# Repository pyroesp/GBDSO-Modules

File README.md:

# GBDSO Modules

This repository will include one or more schematics and PCBs based on the [GBDSO repository](https://github.com/pyroesp/GBDSO).  
In here I'll be making modules of the GBDSO schematic so that I can test them individually.  

A motherboard PCB will also be made so that all modules can be attached to each other and tested as a whole.  

Not sure yet how I'm going to set this up, but I'd like to keep everything related to the modules and motherboard in this repository.

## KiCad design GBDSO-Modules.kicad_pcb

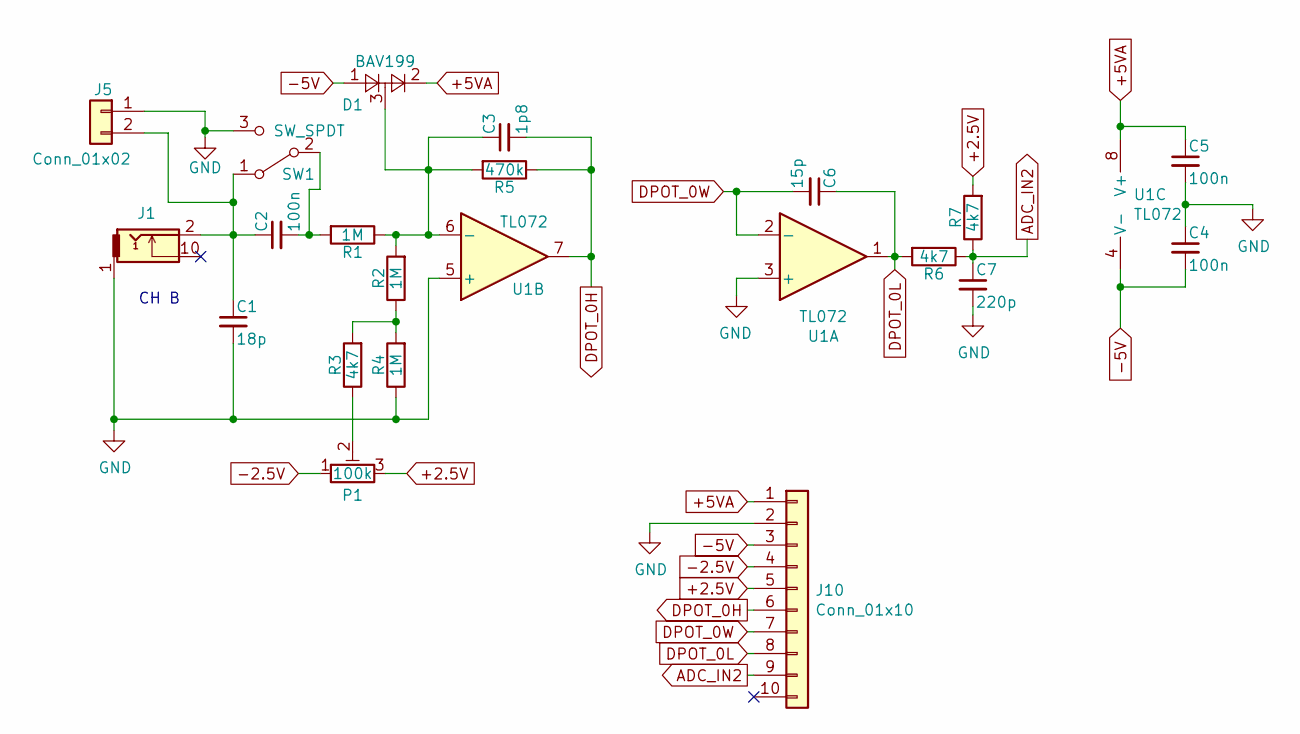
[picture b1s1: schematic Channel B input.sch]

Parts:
C1: 18p; C_0805_2012Metric
C2, C4, C5: 100n; C_0805_2012Metric
C3: 1p8; C_0805_2012Metric
C6: 15p; C_0805_2012Metric
C7: 220p; C_0805_2012Metric
D1: BAV199; SOT-23_Handsoldering
J1: MJ-3523-SMT-TR
J5: Conn_01x02; PinHeader_1x02_P2.54mm_Horizontal
J10: Conn_01x10; DIP-10_W10.16mm
P1: 100k; Potentiometer_Vishay_TS53YJ_Vertical
R1, R2, R4: 1M; R_0805_2012Metric
R3, R6, R7: 4k7; R_0805_2012Metric
R5: 470k; R_0805_2012Metric
SW1: SW_SPDT; SW_SPDT_CK-JS102011SAQN
U1: TL072; SOIC-8_3.9x4.9mm_P1.27mm

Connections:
+2.5V: J10.5, P1.3, R7.2; also elsewhere on the board
+5VA: C5.1, D1.2, J10.1, U1.8 (V+); also elsewhere on the board
-2.5V: J10.4, P1.1; also elsewhere on the board
-5V: C4.2, D1.1, J10.3, U1.4 (V-); also elsewhere on the board
ADC_IN2: C7.1, J10.9, R6.1, R7.1; also elsewhere on the board
DPOT_0H: C3.2, J10.6, R5.1, U1.7; also elsewhere on the board
DPOT_0L: C6.1, J10.8, R6.2, U1.1; also elsewhere on the board
DPOT_0W: C6.2, J10.7, U1.2 (-); also elsewhere on the board
GND: C1.2, C4.1, C5.2, C7.2, J1.1, J5.1, J10.2, R4.1, SW1.3 (C), U1.3 (+), U1.5 (+); also elsewhere on the board
unnamed: C1.1, C2.1, J1.2, J5.2, SW1.1 (A)
unnamed: C2.2, R1.2, SW1.2 (B)
unnamed: C3.1, D1.3, R1.1, R2.2, R5.2, U1.6 (-)
unnamed: P1.2, R3.1
unnamed: R2.1, R3.2, R4.2

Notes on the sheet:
CH B

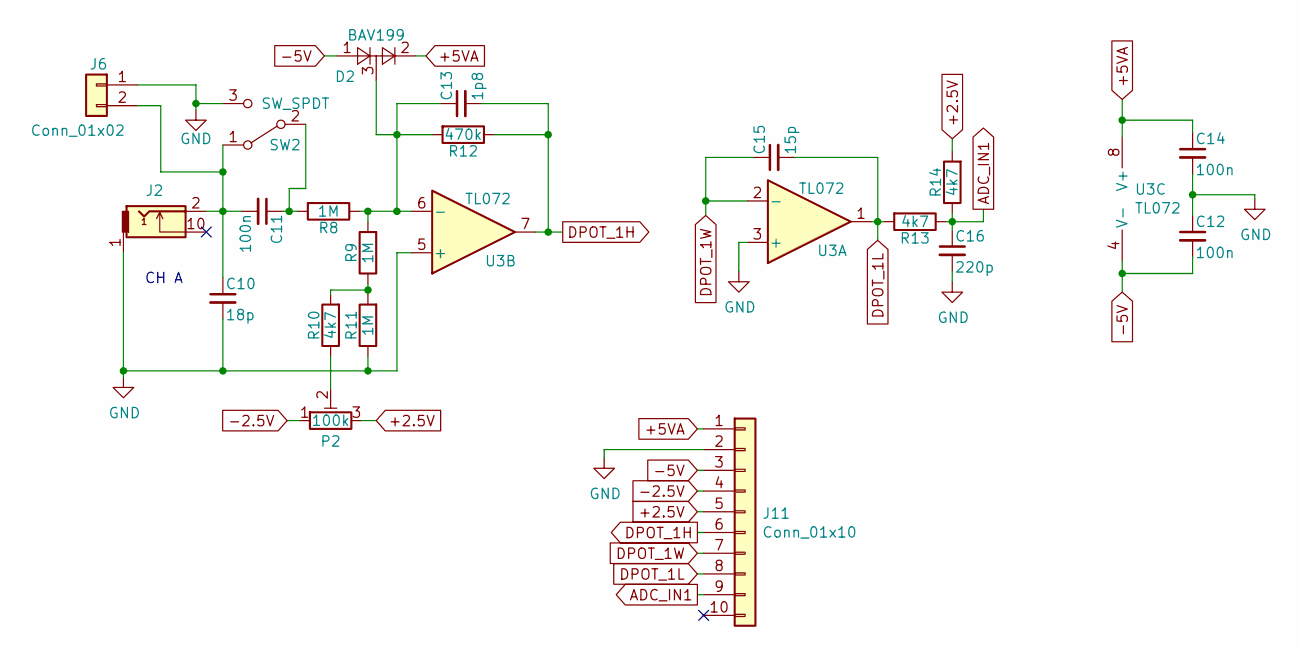
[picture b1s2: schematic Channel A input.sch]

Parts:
C10: 18p; C_0805_2012Metric
C11, C12, C14: 100n; C_0805_2012Metric
C13: 1p8; C_0805_2012Metric
C15: 15p; C_0805_2012Metric
C16: 220p; C_0805_2012Metric
D2: BAV199; SOT-23_Handsoldering
J2: MJ-3523-SMT-TR
J6: Conn_01x02; PinHeader_1x02_P2.54mm_Horizontal
J11: Conn_01x10; DIP-10_W10.16mm
P2: 100k; Potentiometer_Vishay_TS53YJ_Vertical
R8, R9, R11: 1M; R_0805_2012Metric
R10, R13, R14: 4k7; R_0805_2012Metric
R12: 470k; R_0805_2012Metric
SW2: SW_SPDT; SW_SPDT_CK-JS102011SAQN
U3: TL072; SOIC-8_3.9x4.9mm_P1.27mm

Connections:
+2.5V: J11.5, P2.3, R14.2; also elsewhere on the board
+5VA: C14.1, D2.2, J11.1, U3.8 (V+); also elsewhere on the board
-2.5V: J11.4, P2.1; also elsewhere on the board
-5V: C12.2, D2.1, J11.3, U3.4 (V-); also elsewhere on the board
ADC_IN1: C16.1, J11.9, R13.1, R14.1; also elsewhere on the board
DPOT_1H: C13.2, J11.6, R12.1, U3.7; also elsewhere on the board
DPOT_1L: C15.2, J11.8, R13.2, U3.1; also elsewhere on the board
DPOT_1W: C15.1, J11.7, U3.2 (-); also elsewhere on the board
GND: C10.2, C12.1, C14.2, C16.2, J2.1, J6.1, J11.2, R11.1, SW2.3 (C), U3.3 (+), U3.5 (+); also elsewhere on the board
unnamed: C10.1, C11.2, J2.2, J6.2, SW2.1 (A)
unnamed: C11.1, R8.2, SW2.2 (B)
unnamed: C13.1, D2.3, R8.1, R9.2, R12.2, U3.6 (-)
unnamed: P2.2, R10.1
unnamed: R9.1, R10.2, R11.2

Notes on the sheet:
CH A

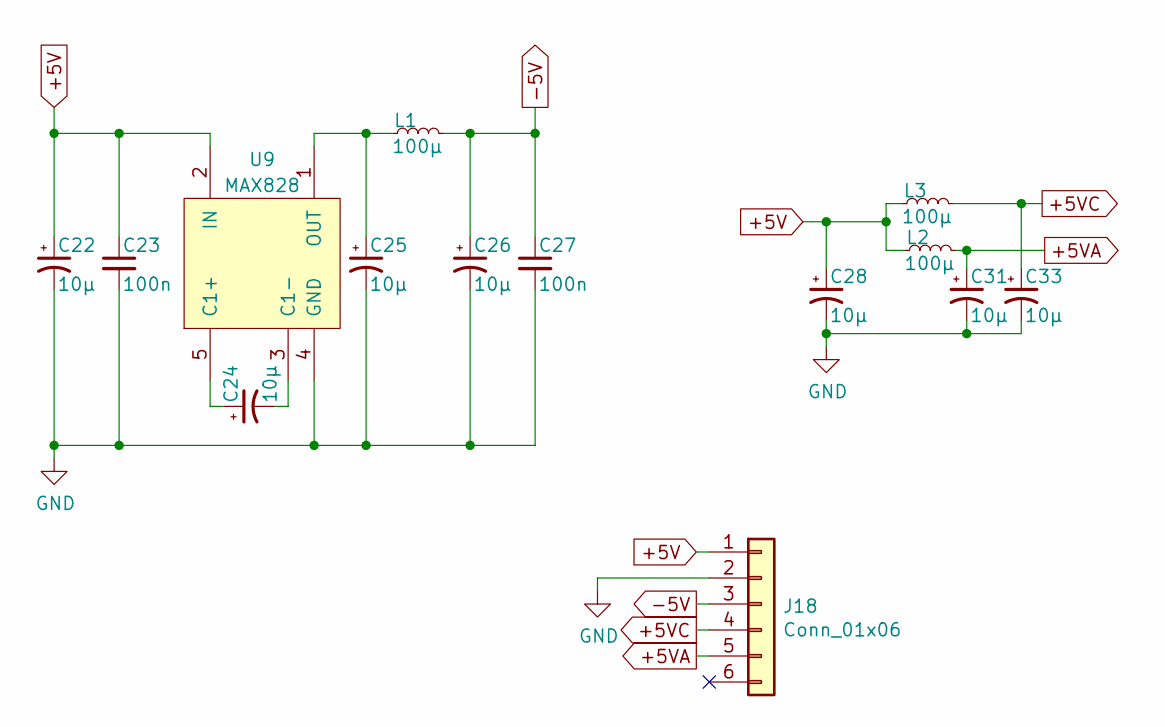
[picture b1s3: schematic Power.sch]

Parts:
C22, C24, C25, C26, C28, C31, C33: 10µ; C_1206_3216Metric
C23, C27: 100n; C_0805_2012Metric
J18: Conn_01x06; DIP-6_W7.62mm
L1, L2, L3: 100µ; L_0805_2012Metric_Pad1.15x1.40mm_HandSolder
U9: MAX828; SOT-23-5_HandSoldering

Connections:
+5V: C22.1, C23.1, C28.1, J18.1, L2.1, L3.1, U9.2 (IN); also elsewhere on the board
+5VA: C31.1, J18.5, L2.2; also elsewhere on the board
+5VC: C33.1, J18.4, L3.2; also elsewhere on the board
-5V: C26.1, C27.1, J18.3, L1.2; also elsewhere on the board
GND: C22.2, C23.2, C25.2, C26.2, C27.2, C28.2, C31.2, C33.2, J18.2, U9.4 (GND); also elsewhere on the board
unnamed: C24.1, U9.5 (C1+)
unnamed: C24.2, U9.3 (C1-)
unnamed: C25.1, L1.1, U9.1 (OUT)

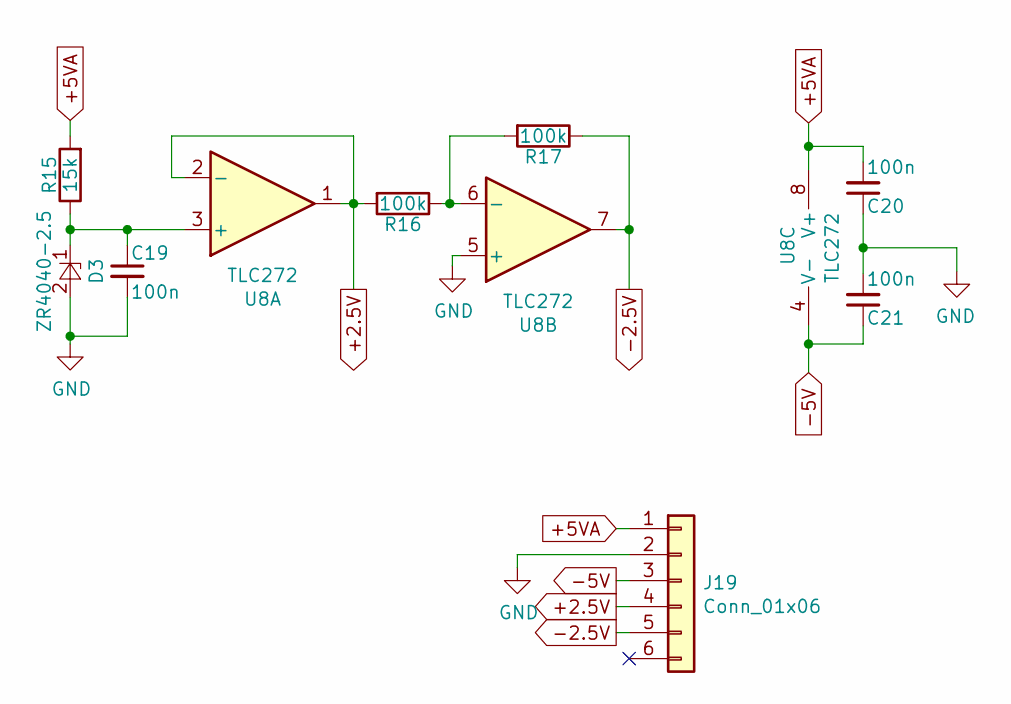
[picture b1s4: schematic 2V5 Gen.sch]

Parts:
C19, C20, C21: 100n; C_0805_2012Metric
D3: ZR4040-2.5; SOT-23_Handsoldering
J19: Conn_01x06; DIP-6_W10.16mm
R15: 15k; R_0805_2012Metric
R16, R17: 100k; R_0805_2012Metric
U8: TLC272; SOIC-8_3.9x4.9mm_P1.27mm

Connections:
+2.5V: J19.4, R16.2, U8.1, U8.2 (-); also elsewhere on the board
+5VA: C20.2, J19.1, R15.2, U8.8 (V+); also elsewhere on the board
-2.5V: J19.5, R17.1, U8.7; also elsewhere on the board
-5V: C21.1, J19.3, U8.4 (V-); also elsewhere on the board
GND: C19.2, C20.1, C21.2, D3.2, J19.2, U8.5 (+); also elsewhere on the board
unnamed: C19.1, D3.1, R15.1, U8.3 (+)
unnamed: R16.1, R17.2, U8.6 (-)

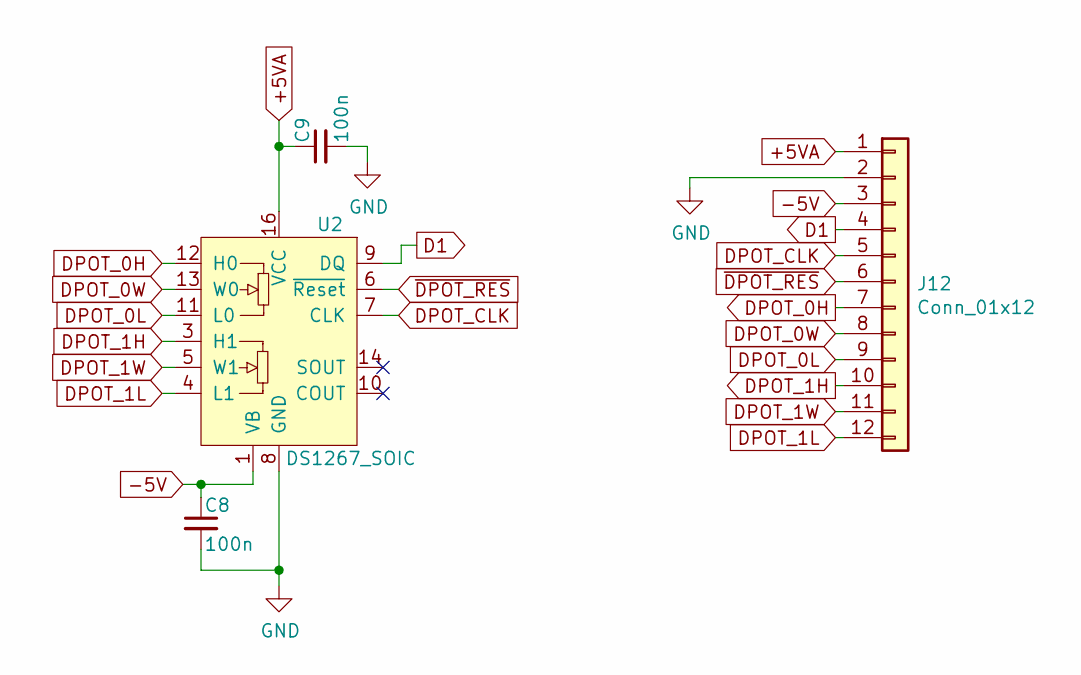
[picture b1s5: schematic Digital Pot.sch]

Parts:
C8, C9: 100n; C_0805_2012Metric
J12: Conn_01x12; PinHeader_1x12_P2.54mm_Vertical
U2: DS1267_SOIC; SOIC-16W_7.5x10.3mm_P1.27mm

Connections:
+5VA: C9.1, J12.1, U2.16 (VCC); also elsewhere on the board
-5V: C8.1, J12.3, U2.1 (VB); also elsewhere on the board
D1: J12.4, U2.9 (DQ); also elsewhere on the board
DPOT_0H: J12.7, U2.12 (H0); also elsewhere on the board
DPOT_0L: J12.9, U2.11 (L0); also elsewhere on the board
DPOT_0W: J12.8, U2.13 (W0); also elsewhere on the board
DPOT_1H: J12.10, U2.3 (H1); also elsewhere on the board
DPOT_1L: J12.12, U2.4 (L1); also elsewhere on the board
DPOT_1W: J12.11, U2.5 (W1); also elsewhere on the board
DPOT_CLK: J12.5, U2.7 (CLK); also elsewhere on the board
GND: C8.2, C9.2, J12.2, U2.8 (GND); also elsewhere on the board
~DPOT_RES: J12.6, U2.6 (~Reset); also elsewhere on the board

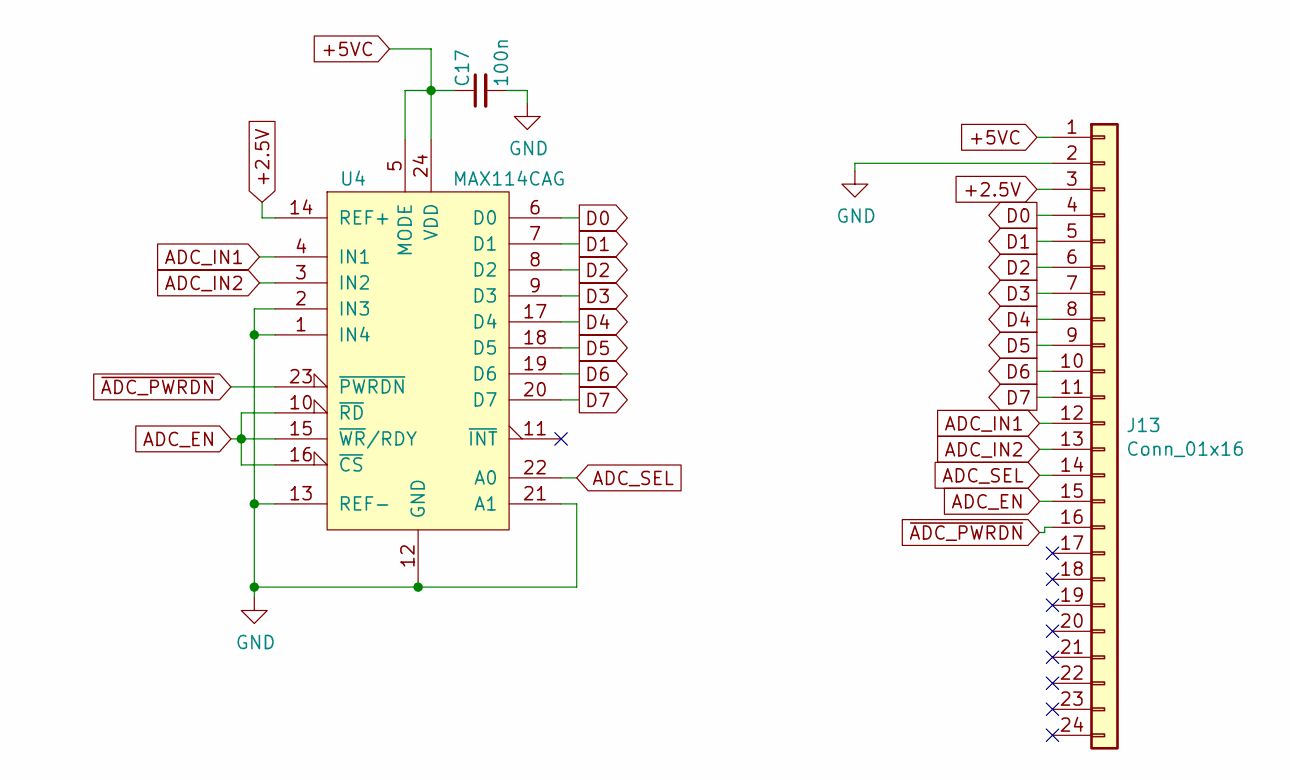
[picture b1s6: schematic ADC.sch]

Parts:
C17: 100n; C_0805_2012Metric
J13: Conn_01x16; DIP-24_W15.24mm
U4: MAX114CAG; SSOP-24_5.3x8.2mm_P0.65mm

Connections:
+2.5V: J13.3, U4.14 (REF+); also elsewhere on the board
+5VC: C17.1, J13.1, U4.5 (MODE), U4.24 (VDD); also elsewhere on the board
ADC_EN: J13.15, U4.10 (~RD), U4.15 (~WR~/RDY), U4.16 (~CS); also elsewhere on the board
ADC_IN1: J13.12, U4.4 (IN1); also elsewhere on the board
ADC_IN2: J13.13, U4.3 (IN2); also elsewhere on the board
ADC_SEL: J13.14, U4.22 (A0); also elsewhere on the board
D0: J13.4, U4.6 (D0); also elsewhere on the board
D1: J13.5, U4.7 (D1); also elsewhere on the board
D2: J13.6, U4.8 (D2); also elsewhere on the board
D3: J13.7, U4.9 (D3); also elsewhere on the board
D4: J13.8, U4.17 (D4); also elsewhere on the board
D5: J13.9, U4.18 (D5); also elsewhere on the board
D6: J13.10, U4.19 (D6); also elsewhere on the board
D7: J13.11, U4.20 (D7); also elsewhere on the board
GND: C17.2, J13.2, U4.1 (IN4), U4.2 (IN3), U4.12 (GND), U4.13 (REF-), U4.21 (A1); also elsewhere on the board
~ADC_PWRDN: J13.16, U4.23 (~PWRDN); also elsewhere on the board

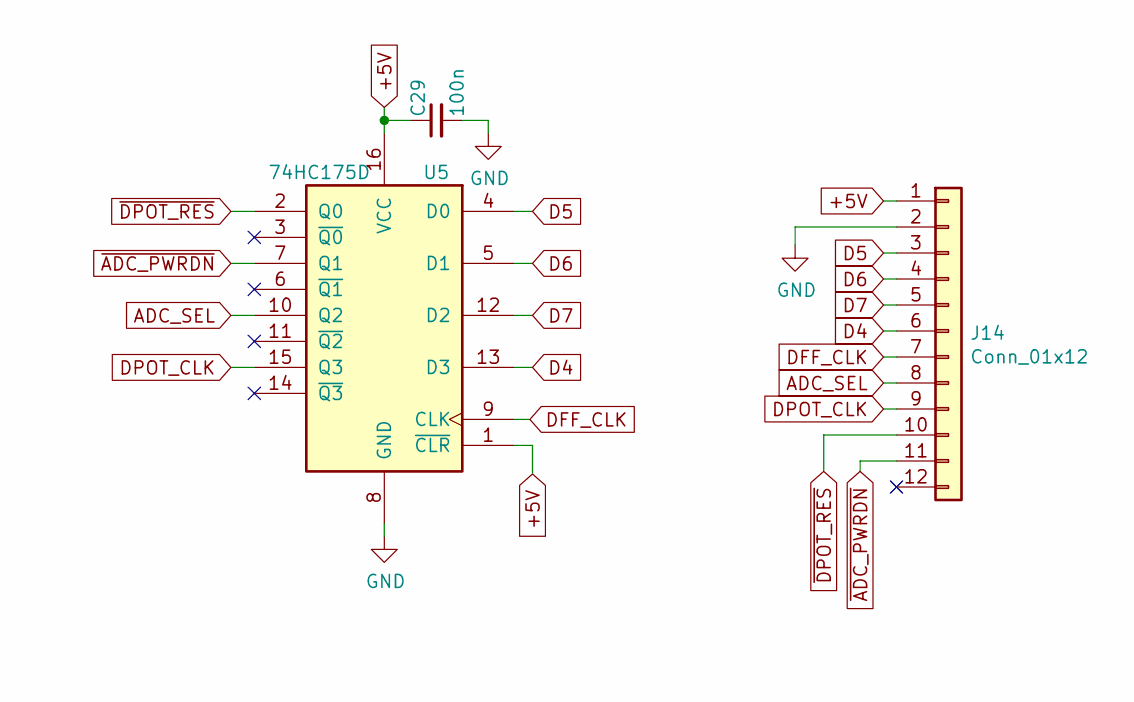
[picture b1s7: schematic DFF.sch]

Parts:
C29: 100n; C_0805_2012Metric
J14: Conn_01x12; DIP-12_W10.16mm_LongPads
U5: 74HC175D; SOIC-16_3.9x9.9mm_P1.27mm

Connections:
+5V: C29.1, J14.1, U5.1 (~CLR), U5.16 (VCC); also elsewhere on the board
ADC_SEL: J14.8, U5.10 (Q2); also elsewhere on the board
D4: J14.6, U5.13 (D3); also elsewhere on the board
D5: J14.3, U5.4 (D0); also elsewhere on the board
D6: J14.4, U5.5 (D1); also elsewhere on the board
D7: J14.5, U5.12 (D2); also elsewhere on the board
DFF_CLK: J14.7, U5.9 (CLK); also elsewhere on the board
DPOT_CLK: J14.9, U5.15 (Q3); also elsewhere on the board
GND: C29.2, J14.2, U5.8 (GND); also elsewhere on the board
~ADC_PWRDN: J14.11, U5.7 (Q1); also elsewhere on the board
~DPOT_RES: J14.10, U5.2 (Q0); also elsewhere on the board

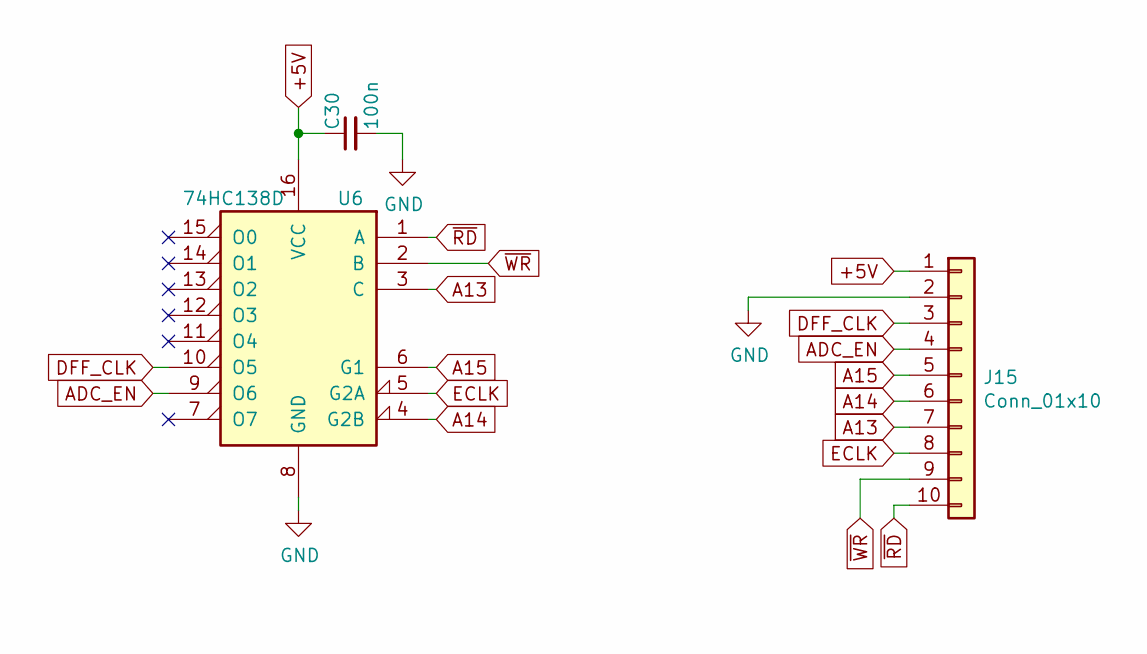
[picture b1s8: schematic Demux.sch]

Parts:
C30: 100n; C_0805_2012Metric
J15: Conn_01x10; DIP-10_W10.16mm
U6: 74HC138D; SOIC-16_3.9x9.9mm_P1.27mm

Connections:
+5V: C30.1, J15.1, U6.16 (VCC); also elsewhere on the board
A13: J15.7, U6.3 (C); also elsewhere on the board
A14: J15.6, U6.4 (G2B); also elsewhere on the board
A15: J15.5, U6.6 (G1); also elsewhere on the board
ADC_EN: J15.4, U6.9 (O6); also elsewhere on the board
DFF_CLK: J15.3, U6.10 (O5); also elsewhere on the board
ECLK: J15.8, U6.5 (G2A); also elsewhere on the board
GND: C30.2, J15.2, U6.8 (GND); also elsewhere on the board
~RD: J15.10, U6.1 (A); also elsewhere on the board
~WR: J15.9, U6.2 (B); also elsewhere on the board

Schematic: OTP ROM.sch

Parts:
C18: 100n; C_0805_2012Metric
J16: Conn_01x28; DIP-28_W7.62mm
JP1: SolderJumper_3_Open; SolderJumper-3_P1.3mm_Open_RoundedPad1.0x1.5mm_NumberLabels
U7: AT27C256R; PLCC-32_HandSolder

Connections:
+5V: C18.1, J16.1, JP1.3 (B), U7.32 (VCC); also elsewhere on the board
A0: J16.5, U7.11 (A0); also elsewhere on the board
A1: J16.6, U7.10 (A1); also elsewhere on the board
A2: J16.7, U7.9 (A2); also elsewhere on the board
A3: J16.8, U7.8 (A3); also elsewhere on the board
A4: J16.9, U7.7 (A4); also elsewhere on the board
A5: J16.10, U7.6 (A5); also elsewhere on the board
A6: J16.11, U7.5 (A6); also elsewhere on the board
A7: J16.12, U7.4 (A7); also elsewhere on the board
A8: J16.13, U7.29 (A8); also elsewhere on the board
A9: J16.14, U7.28 (A9); also elsewhere on the board
A10: J16.15, U7.24 (A10); also elsewhere on the board
A11: J16.16, U7.27 (A11); also elsewhere on the board
A12: J16.17, U7.3 (A12); also elsewhere on the board
A13: J16.18, U7.30 (A13); also elsewhere on the board
A14: J16.19, U7.31 (A14); also elsewhere on the board
A15: J16.20, U7.23 (~CE); also elsewhere on the board
D0: J16.21, U7.13 (D0); also elsewhere on the board
D1: J16.22, U7.14 (D1); also elsewhere on the board
D2: J16.23, U7.15 (D2); also elsewhere on the board
D3: J16.24, U7.18 (D3); also elsewhere on the board
D4: J16.25, U7.19 (D4); also elsewhere on the board
D5: J16.26, U7.20 (D5); also elsewhere on the board
D6: J16.27, U7.21 (D6); also elsewhere on the board
D7: J16.28, U7.22 (D7); also elsewhere on the board
GND: C18.2, J16.2, U7.16 (GND); also elsewhere on the board
unnamed: JP1.2 (C), U7.2 (VPP)
VPP: J16.4, JP1.1 (A); also elsewhere on the board
~RD: J16.3, U7.25 (~OE); also elsewhere on the board

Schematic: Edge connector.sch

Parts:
J3: Edge Connector; GB_EdgeConnector
J17: Conn_01x32; DIP-32_W7.62mm

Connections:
+5V: J3.1, J17.1; also elsewhere on the board
A0: J3.6, J17.7; also elsewhere on the board
A1: J3.7, J17.8; also elsewhere on the board
A2: J3.8, J17.9; also elsewhere on the board
A3: J3.9, J17.10; also elsewhere on the board
A4: J3.10, J17.11; also elsewhere on the board
A5: J3.11, J17.12; also elsewhere on the board
A6: J3.12, J17.13; also elsewhere on the board
A7: J3.13, J17.14; also elsewhere on the board
A8: J3.14, J17.15; also elsewhere on the board
A9: J3.15, J17.16; also elsewhere on the board
A10: J3.16, J17.17; also elsewhere on the board
A11: J3.17, J17.18; also elsewhere on the board
A12: J3.18, J17.19; also elsewhere on the board
A13: J3.19, J17.20; also elsewhere on the board
A14: J3.20, J17.21; also elsewhere on the board
A15: J3.21, J17.22; also elsewhere on the board
D0: J3.22, J17.23; also elsewhere on the board
D1: J3.23, J17.24; also elsewhere on the board
D2: J3.24, J17.25; also elsewhere on the board
D3: J3.25, J17.26; also elsewhere on the board
D4: J3.26, J17.27; also elsewhere on the board
D5: J3.27, J17.28; also elsewhere on the board
D6: J3.28, J17.29; also elsewhere on the board
D7: J3.29, J17.30; also elsewhere on the board
ECLK: J3.2, J17.3; also elsewhere on the board
GND: J3.32, J17.2; also elsewhere on the board
VPP: J3.5, J17.6; also elsewhere on the board
~RD: J3.4, J17.5; also elsewhere on the board
~WR: J3.3, J17.4; also elsewhere on the board

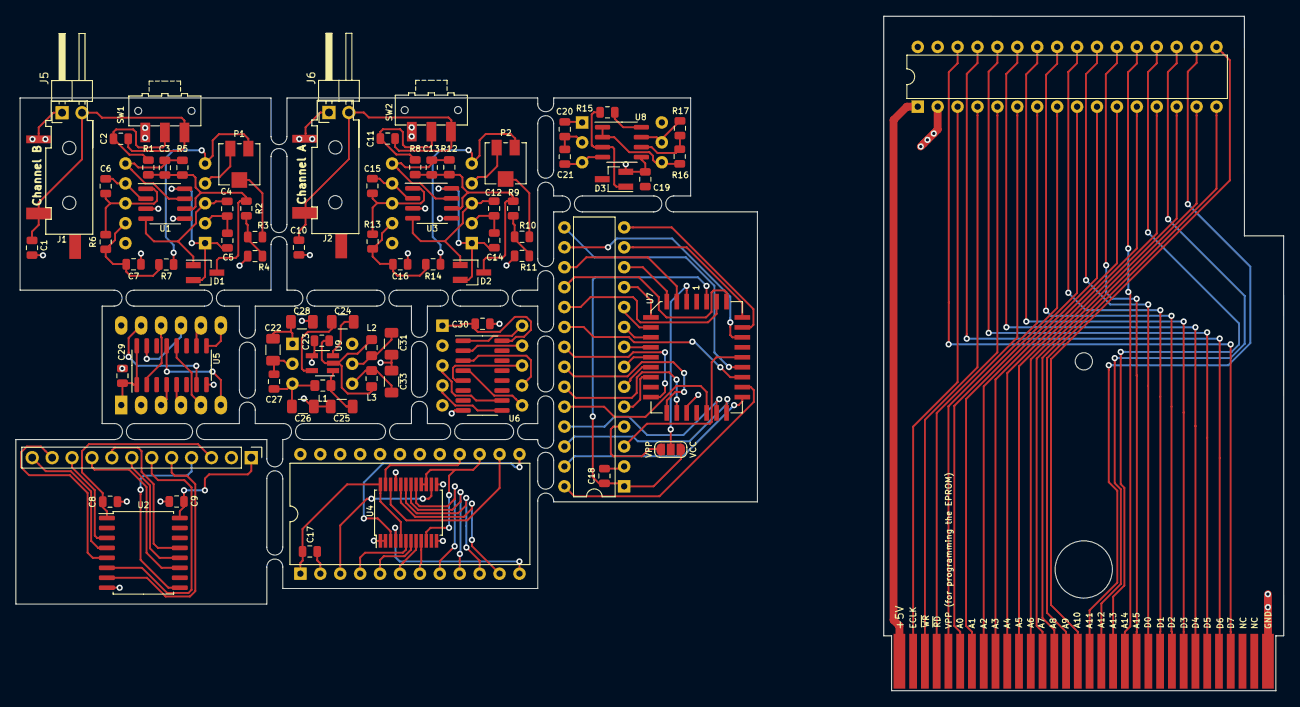
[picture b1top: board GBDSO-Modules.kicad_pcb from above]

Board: 2 copper layers, 94.6 x 64.5 mm, 84 parts (0 on the bottom side), 65 nets.

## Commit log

2020-04-02 explaining purpose of repo in the readme
2020-04-04 fix title
2020-04-04 setting up this repo with files from the GBDSO repo
    setup kicad project, copied schematic, copied components
2020-04-04 separated each module into a different sheet, started the pcb
2020-04-04 added autosave to ignore list
2020-04-04 C8 on the dig pot wasn't connected correctly
    changed the schematic, updated the netlist and PCB
2020-04-05 fixed schematic and updated PCB
    Fixed the schematic after having found the issues in the GBDSO schematic (which is also fixed on the repo).
    Continued making the PCB for the modules. We're not at 7 modules from 10.
2020-04-12 added the PLCC32 handsolder footprint I made on the other repo here
2020-04-12 pin 10 of J12 was not connected to the correct signal, fixed
2020-04-12 Finished and panelized the PCBs, except for edge connector; too big
2020-04-12 forgot to add the ground plane on the panel, fixed
